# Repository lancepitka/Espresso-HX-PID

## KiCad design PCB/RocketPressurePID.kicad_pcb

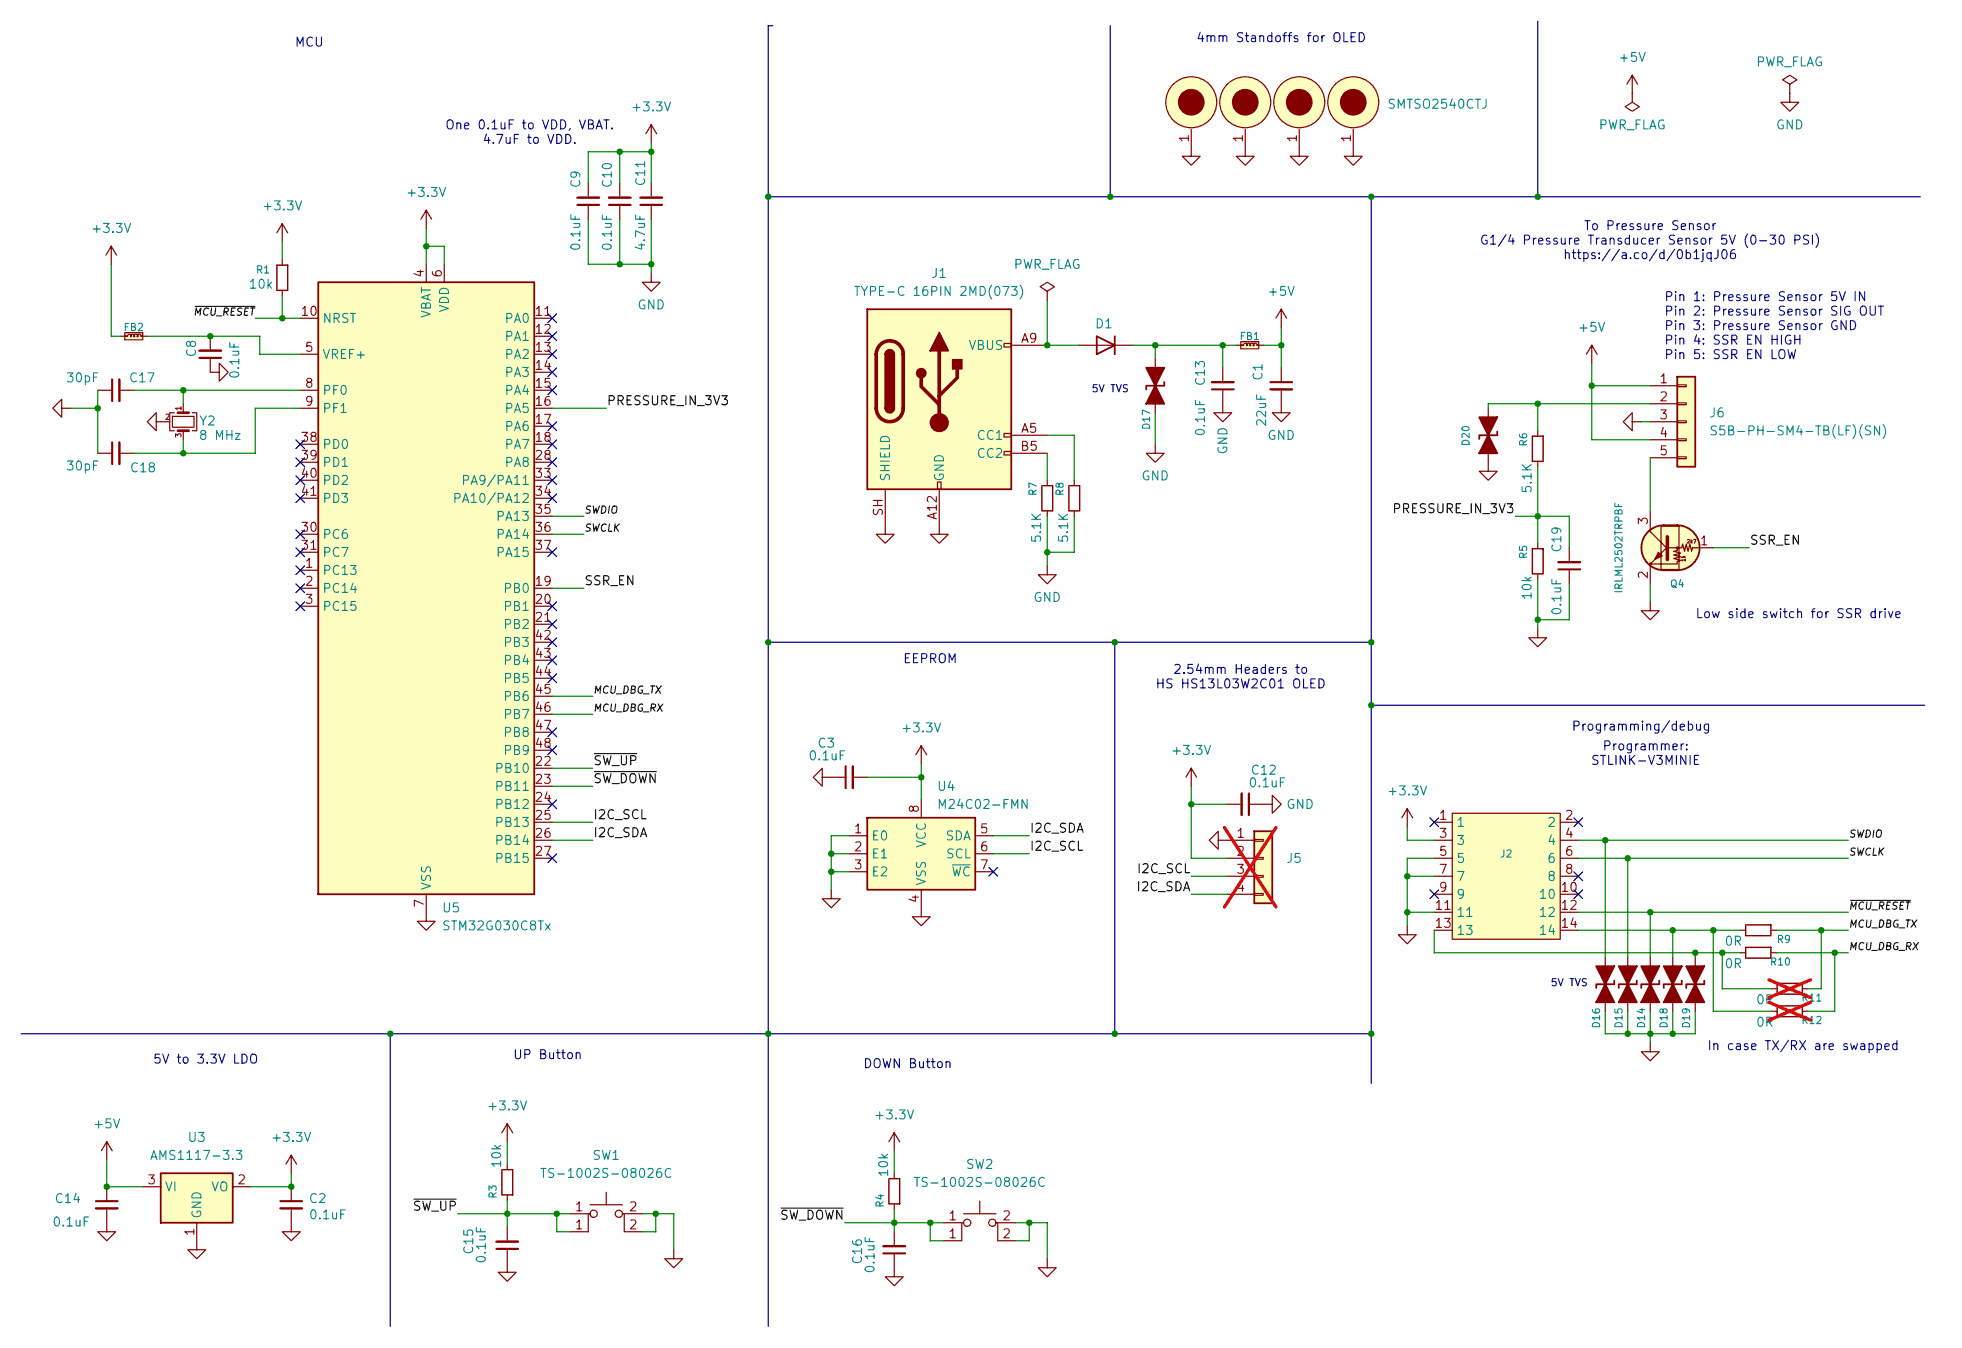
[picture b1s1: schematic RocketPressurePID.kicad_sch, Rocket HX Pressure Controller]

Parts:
C1: 22uF; C_0603_1608Metric; LCSC C59461
C2, C3, C8, C9, C10, C12, C13, C14, C15, C16, C19: 0.1uF; C_0603_1608Metric; LCSC C14663
C11: 4.7uF; C_0603_1608Metric; LCSC C19666
C17, C18: 30pF; C_0603_1608Metric; LCSC C1658
D1: Nexperia_CFP3_SOD-123W; LCSC C8598
D14, D15, D16, D17, D18, D19, D20: 5V_TVS; D_SOD-323; LCSC C2835457
FB1, FB2: BLM18PG330SN1D; L_0603_1608Metric; Part Number BLM18PG330SN1D; LCSC C1002
J1: TYPE-C 16PIN 2MD(073); USB_C_Receptacle_GCT_USB4105-xx-A_16P_TopMnt_Horizontal; LCSC C2765186
J2: 2x14 1.27mm SMD; PinHeader_2x07_P1.27mm_Vertical_SMD; LCSC C41376039
J5: PinHeader_1x04_P2.54mm_Vertical; LCSC C2691448; not fitted
J6: S5B-PH-SM4-TB(LF)(SN); JST_PH_S5B-PH-SM4-TB_1x05-1MP_P2.00mm_Horizontal; LCSC C265104
Q4: IRLML2502TRPBF; SOT-23; Part Number IRLML2502TRPBF; LCSC C2589
R1, R3, R4, R5: 10k; R_0603_1608Metric; LCSC C25804
R6, R7, R8: 5.1K; R_0603_1608Metric; LCSC C23186
R9, R10: 0R; R_0603_1608Metric; LCSC C21189
R11, R12: 0R; R_0603_1608Metric; LCSC C21189; not fitted
STD1, STD2, STD3, STD4: SMTSO2540CTJ; standoff_SMTSO2540CTJ; LCSC C2916324
SW1, SW2: TS-1002S-08026C; SW_SPST_PTS645Sx43SMTR92; LCSC C455116
U3: AMS1117-3.3; SOT-223-3_TabPin2; LCSC C6186
U4: M24C02-FMN; SOIC-8_3.9x4.9mm_P1.27mm
U5: STM32G030C8Tx; LQFP-48_7x7mm_P0.5mm; LCSC C529329
Y2: 8 MHz; Crystal_SMD_3225-4Pin_3.2x2.5mm; LCSC C2682774

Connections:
+3.3V: C2.1, C3.2, C9.2, C10.2, C11.2, C12.2, FB2.2, J2.3, J5.2, R1.1, R3.2, R4.2, U3.2 (VO), U4.8 (VCC), U5.4 (VBAT), U5.6 (VDD)
+5V: C1.1, C14.1, FB1.1, J6.1, J6.4, U3.3 (VI)
/I2C_SCL: J5.3, U4.6 (SCL), U5.25 (PB13)
/I2C_SDA: J5.4, U4.5 (SDA), U5.26 (PB14)
/MCU_DBG_RX: R10.1, R12.1, U5.46 (PB7)
/MCU_DBG_TX: R9.1, R11.1, U5.45 (PB6)
/PRESSURE_IN_3V3: C19.2, R5.1, R6.2, U5.16 (PA5)
/SSR_EN: Q4.1 (B), U5.19 (PB0)
/SWCLK: D15.1 (A1), J2.6, U5.36 (PA14)
/SWDIO: D16.1 (A1), J2.4, U5.35 (PA13)
/~MCU_RESET: D14.1 (A1), J2.12, R1.2, U5.10 (NRST)
/~SW_DOWN: C16.2, R4.1, SW2.1, U5.23 (PB11)
/~SW_UP: C15.2, R3.1, SW1.1, U5.22 (PB10)
GND: C1.2, C2.2, C3.1, C8.1, C9.1, C10.1, C11.1, C12.1, C13.1, C14.2, C15.1, C16.1, C17.1, C18.1, C19.1, D14.2 (A2), D15.2 (A2), D16.2 (A2), D17.2 (A2), D18.2 (A2), D19.2 (A2), D20.2 (A2), J1.A1 (GND), J1.A12 (GND), J1.B1 (GND), J1.B12 (GND), J1.SH (SHIELD), J2.5, J2.7, J2.11, J5.1, J6.3, Q4.2 (E), R5.2, R7.2, R8.2, STD1.1, STD2.1, STD3.1, STD4.1, SW1.2, SW2.2, U3.1 (GND), U4.1 (E0), U4.2 (E1), U4.3 (E2), U4.4 (VSS), U5.7 (VSS), Y2.2 (G), Y2.4 (G)
unnamed: D1.2 (A), J1.A4 (VBUS), J1.A9 (VBUS), J1.B4 (VBUS), J1.B9 (VBUS)
unnamed: C13.2, D1.1 (K), D17.1 (A1), FB1.2
unnamed: D18.1 (A1), J2.14, R9.2, R12.2
unnamed: D19.1 (A1), J2.13, R10.2, R11.2
unnamed: D20.1 (A1), J6.2, R6.1
unnamed: J1.A5 (CC1), R8.1
unnamed: J1.B5 (CC2), R7.1
unnamed: J6.5, Q4.3 (C)
unnamed: C17.2, U5.8 (PF0), Y2.1
unnamed: C18.2, U5.9 (PF1), Y2.3
unnamed: C8.2, FB2.1, U5.5 (VREF+)

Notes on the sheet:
UP Button
2.54mm Headers to HS HS13L03W2C01 OLED
One 0.1uF to VDD, VBAT. 4.7uF to VDD.
5V to 3.3V LDO
Pin 1: Pressure Sensor 5V IN Pin 2: Pressure Sensor SIG OUT Pin 3: Pressure Sensor GND Pin 4: SSR EN HIGH Pin 5: SSR EN LOW
5V TVS
DOWN Button
Programming/debug
In case TX/RX are swapped
4mm Standoffs for OLED
Low side switch for SSR drive
MCU
EEPROM
Programmer: STLINK-V3MINIE
To Pressure Sensor G1/4 Pressure Transducer Sensor 5V (0-30 PSI) https://a.co/d/0b1jqJ06

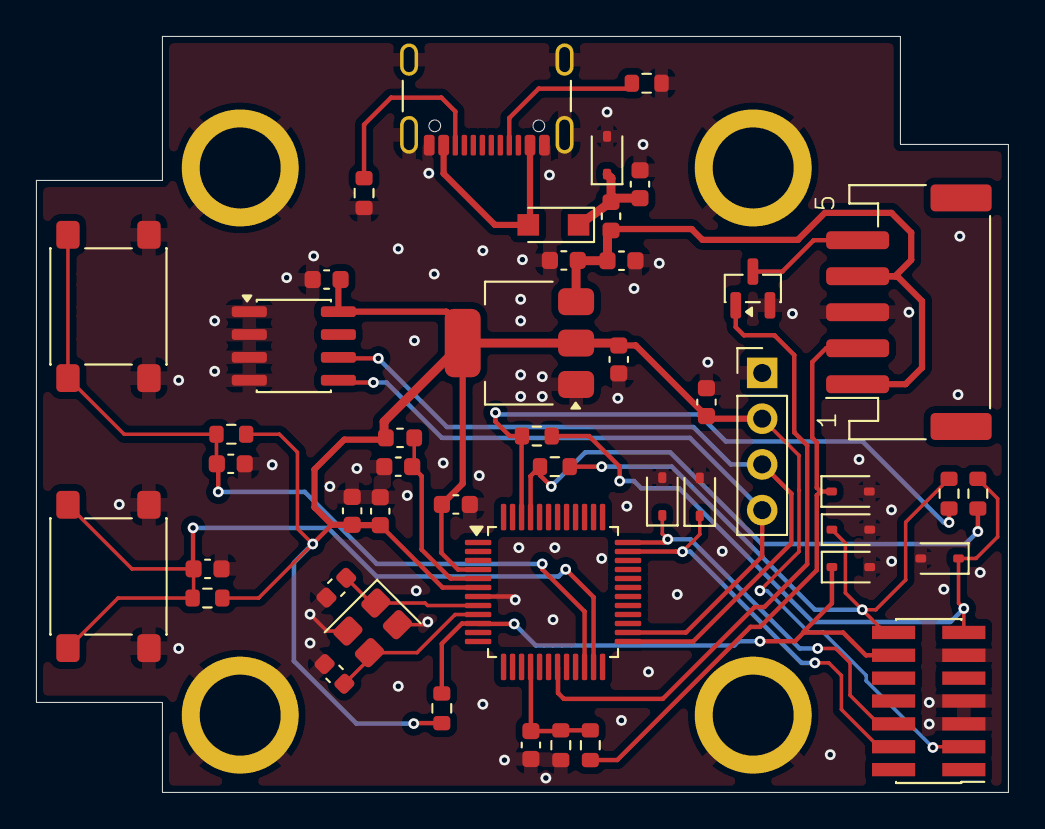
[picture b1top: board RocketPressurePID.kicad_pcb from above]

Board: 2 copper layers, 54.0 x 42.0 mm, 52 parts (0 on the bottom side), 25 nets.

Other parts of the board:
U2: HS HS13L03W2C01; HS13L03W2C01

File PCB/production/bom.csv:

Designator,Footprint,Quantity,Value,LCSC Part #
C1,0603,1,22uF,C59461
"C10, C12, C13, C14, C15, C16, C19, C2, C3, C8, C9",0603,11,0.1uF,C14663
C11,0603,1,4.7uF,C19666
"C17, C18",0603,2,30pF,C1658
D1,Nexperia_CFP3_SOD-123W,1,~,C8598
"D14, D15, D16, D17, D18, D19, D20",D_SOD-323,7,5V_TVS,C2835457
"FB1, FB2",0603,2,BLM18PG330SN1D,C1002
J1,USB_C_Receptacle_GCT_USB4105-xx-A_16P_TopMnt_Horizontal,1,TYPE-C 16PIN 2MD(073),C2765186
J2,PinHeader_2x07_P1.27mm_Vertical_SMD,1,2x14 1.27mm SMD,C41376039
J6,JST_PH_S5B-PH-SM4-TB_1x05-1MP_P2.00mm_Horizontal,1,S5B-PH-SM4-TB(LF)(SN),C265104
Q4,SOT-23,1,IRLML2502TRPBF,C2589
"R1, R3, R4, R5",0603,4,10k,C116677
"R10, R9",0603,2,0R,C21189
"R6, R7, R8",0603,3,5.1K,C23186
"STD1, STD2, STD3, STD4",standoff_SMTSO2540CTJ,4,SMTSO2540CTJ,C2916324
"SW1, SW2",SW_SPST_PTS645Sx43SMTR92,2,TS-1002S-08026C,C455116
U3,SOT-223-3_TabPin2,1,AMS1117-3.3,C6186
U4,SOIC-8_3.9x4.9mm_P1.27mm,1,M24C02-FMN,
U5,LQFP-48_7x7mm_P0.5mm,1,STM32G030C8Tx,C529329
Y2,Crystal_SMD_3225-4Pin_3.2x2.5mm,1,8 MHz,C2682774

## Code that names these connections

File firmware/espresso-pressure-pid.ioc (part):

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Mcu.Name=STM32G030C(6-8)Tx
Mcu.Package=LQFP48
Mcu.UserName=STM32G030C8Tx
PA13.Mode=Serial_Wire
PA13.Signal=SYS_SWDIO
PA14-BOOT0.Mode=Serial_Wire
PA14-BOOT0.Signal=SYS_SWCLK
PA5.Mode=IN5
PA5.Signal=ADC1_IN5
PB0.GPIOParameters=GPIO_Label
PB0.GPIO_Label=SSR_EN
PB0.Signal=GPIO_Output
PB10.GPIOParameters=GPIO_Label
PB10.GPIO_Label=nSW_UP
PB10.Signal=GPIO_Input
PB11.GPIOParameters=GPIO_Label
PB11.GPIO_Label=nSW_DOWN
PB11.Signal=GPIO_Input
PB13.Mode=I2C
PB13.Signal=I2C2_SCL
PB14.Mode=I2C
PB14.Signal=I2C2_SDA
PB6.GPIOParameters=GPIO_Speed
PB6.GPIO_Speed=GPIO_SPEED_FREQ_VERY_HIGH
PB6.Mode=Asynchronous
PB6.Signal=USART1_TX
PB7.GPIOParameters=GPIO_Speed
PB7.GPIO_Speed=GPIO_SPEED_FREQ_VERY_HIGH
PB7.Mode=Asynchronous
PB7.Signal=USART1_RX
PF0-OSC_IN\ (PF0).Mode=HSE-External-Oscillator
PF0-OSC_IN\ (PF0).Signal=RCC_OSC_IN
PF1-OSC_OUT\ (PF1).Mode=HSE-External-Oscillator
PF1-OSC_OUT\ (PF1).Signal=RCC_OSC_OUT
RCC.HSE_VALUE=8000000
RCC.SYSCLKFreq_VALUE=32000000
RCC.SYSCLKSource=RCC_SYSCLKSOURCE_PLLCLK
board=custom

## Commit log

2026-06-02 v1.0 manufacturing
2026-06-09 Initial commit of generated firmware project
2026-06-09 Basic firmware project setup
2026-06-09 Basic app layout
2026-06-09 Added logging library
2026-06-10 Added timer
2026-06-10 Updated ADC to continuous conversion mode, 16x over sample ratio (effective 14 bit)
2026-06-18 Fixed launch config
2026-06-18 cmake updates
2026-06-18 Updated clocks
2026-06-18 Got ADC setup and reading properly
2026-06-18 Added adc read api
2026-06-19 Updated alt part number
2026-06-19 Added ADC filtering
2026-06-19 Implemented button driver
2026-06-19 Added SH1106 driver code
2026-06-19 Added display abstradtion and updated cmake
